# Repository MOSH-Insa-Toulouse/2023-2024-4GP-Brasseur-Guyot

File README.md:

# 2023-2024-4GP-Brasseur-Guyot

Projet capteur low-tech en graphite par Damien Brasseur et Tristan Guyot : le **BG0524-LTG**

### Contexte

Ce capteur a été réalisé, instrumenté et caractérisé dans le cadre d'un projet de 4ème année au département du Génie Physique de l'INSA TOULOUSE, encadré par Jérémie Grisolia, Benjamin Mestre, Arnaud Biganzoli et Cathy Crouzet. Tout le code, schématiques et mesures sont *open source* et réutilisables à volonté.

### Contacts

Damien : brasseu@insa-toulouse.fr <br>
Tristan : tguyot@insa-toulouse.fr

### Table des matières

[Description générale du projet](#coo) <br>
[Caractéristiques techniques](#zozo) <br>
[Mode d'emploi](#pookie) <br>
[Tests du capteur graphite](#booboo)

## 1 - Description générale du projet <a name="coo">

### Principe

Les capteurs sont partout. Dès qu’on cherche à automatiser un système, quel qu’il soit, on a besoin de capteurs. Pourtant, la plupart sont très coûteux en énergie, et leur multiplication fait qu’ils sont de plus en plus impactants sur l’environnement. C’est pour ça que les capteurs low-tech représentent un atout non négligeable. 

Un dépôt de graphite sur du papier forme un système granulaire, composé de grains de plus ou moins grande taille espacés d'une certaine distance, appelée distance inter-grain.
Cette propriété fait que sa conductance dépend de façon exponentielle de la distance inter-grain, qui peut être modulée en repliant le papier.
Ainsi, on peut retrouver la contrainte appliquée au matériau directement en mesurant la résistance aux bornes du capteur.

### Contenu du banc

 <br>

 - Le capteur graphite (interchangeable)
 - Un amplificateur permettant de mesurer avec précision les variations (cette amplification peut être modulée via la modification de la résistance R2 de la boucle de rétroaction de l'amplificateur, pilotée grâce à l'encodeur rotatoire)
 - Un capteur flex-sensor permettant de comparer les mesures du capteur graphite
 - Un écran OLED, sur lequel les mesures sont affichées en temps-réel
 - Une application Android, connectée en Bluetooth, sur laquelle les mesures et leur variation peuvent être visionnée

## 2 - Caractéristiques techniques <a name="zozo">

La *datasheet* est accessible [ici](./Datasheet/datasheet_capteur-graphite_final.pdf)

### Capteur

Le capteur est constitué d'une feuille de papier recouverte de graphite déposé au crayon selon un patterne spécifique :

 <br>

L'épaisseur du papier utilisé est de 200 µm.

### Electronique

L'électronique analogique permettant d'amplifier et de filtrer le signal du capteur graphite est composé d'un amplificateur transimpédance LTC1050 et de trois filtres :
 - Un filtre passif en entrée permettant d'éviter la distortion dans l'étage d'entrée
 - Un filtre actif basé sur l'amplificateur permettant une efficacité maximale
 - Un filtre passif en sortie pour éliminer le bruit introduit lors du traitement.

 <br>

### KiCad

Explications disponibles [ici](https://github.com/MOSH-Insa-Toulouse/2023-2024-4GP-Brasseur-Guyot/tree/main/KiCad)

### Code Arduino

Explications disponibles [ici](https://github.com/MOSH-Insa-Toulouse/2023-2024-4GP-Brasseur-Guyot/tree/main/Code%20Arduino)

### Application Android

Explications disponibles [ici](https://github.com/MOSH-Insa-Toulouse/2023-2024-4GP-Brasseur-Guyot/tree/main/Application%20Android)

## 3 - Mode d'emploi <a name="pookie">

### KiCad

Le dossier KiCad est à télécharger dans son intégralité.
Une fois téléchargé, il faudra recharger les librairies de symboles depuis le dossier Mods.

### Code Arduino

Pour charger le code sur la carte **Arduino UNO**, rien de plus facile ! Il suffit de l'ouvrir dans l'application Arduino IDE avec la carte branchée en USB, puis cliquer sur *Upload*.

### Application Android

L'application est à télécharger sur un téléphone Android. Après l'installation, aller dans les paramètres des applications Android et accorder l'accès au Bluetooth et au micro à l'application.
Pour assurer la connexion entre la carte Arduino et le téléphone, il faut d'abord se connecter au module Bluetooth de la carte avec l'interface générale Bluetooth du téléphone. Ensuite, on pourra sélectionner dans l'application le module et on pourra commencer à s'amuser.

## 4 - Tests du capteur graphite <a name="booboo">

Nous avons réalisé des mesures de compression et de détente avec des capteurs comportant différentes densités de graphite (variant avec le type de crayon : 4H, HB et 4B), ainsi que pour le Flex sensor.

Le banc de test sur lequel nous avons testé les mesures comporte 4 demi-cercles de diamètres 2cm, 3cm, 4cm et 5cm, respectivement. La déformation est calculée selon l'expression suivante : $\varepsilon = \frac{D}{e}$ avec $D$ diamètre du demi-cercle et $e$ épaisseur du papier.

Voici la caractéristique en détente : 

 <br>

On remarque que la variation de résistance la plus marquée (pente la plus élevée) est cele du capteur au crayon 4H. De façon surprenante, le capteur au cayon HB est moins efficace que le capteur 4B.

Voici la caractéristique en compression : 

 <br>

Même comportement, sauf qu'une limite a été atteinte en mesure de compression (demi-cercle de 2cm) avec le capteur 4H. Le flex sensor ne fonctionnant que dans un seul sens, nous n'avons pas pu le tester dans ces conditions.

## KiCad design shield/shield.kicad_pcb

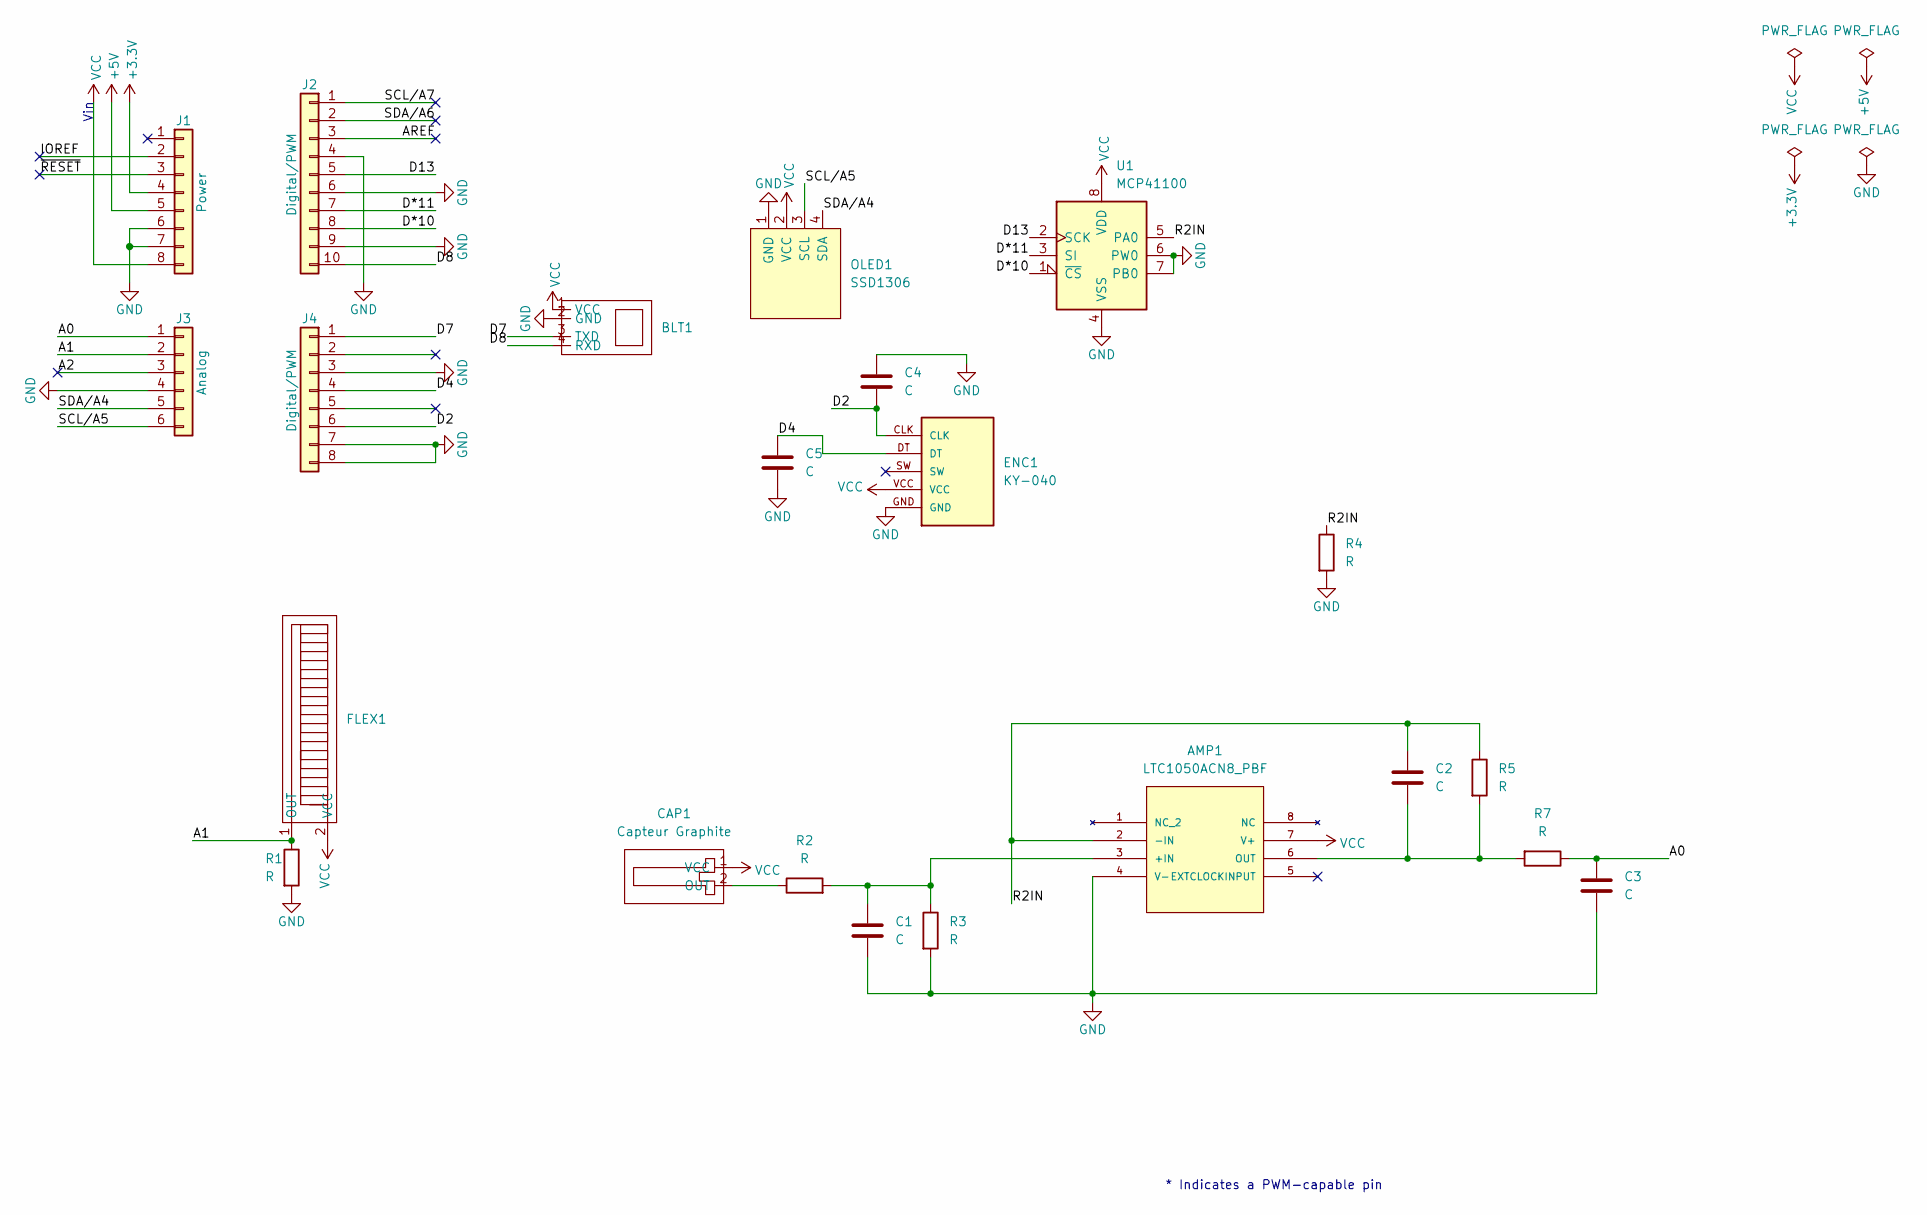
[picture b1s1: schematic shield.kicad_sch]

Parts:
AMP1: LTC1050ACN8_PBF; PDIP-8_N; MANUFACTURER_PART_NUMBER ltc1050acn8
BLT1: PinSocket_1x04_P2.54mm_Vertical
C1, C3, C4, C5: C; C_Disc_D4.7mm_W2.5mm_P5.00mm
C2: C; C_Rect_L4.6mm_W3.8mm_P2.50mm_MKS02_FKP02
CAP1: Capteur Graphite; PinSocket_1x02_P2.54mm_Vertical
ENC1: KY-040; KY-040-PORT
FLEX1: PinSocket_1x02_P2.54mm_Vertical
J1: Power; PinSocket_1x08_P2.54mm_Vertical
J2: Digital/PWM; PinSocket_1x10_P2.54mm_Vertical
J3: Analog; PinSocket_1x06_P2.54mm_Vertical
J4: Digital/PWM; PinSocket_1x08_P2.54mm_Vertical
OLED1: SSD1306; 128x64OLED
R1, R3, R4, R5: R; R_Axial_DIN0207_L6.3mm_D2.5mm_P2.54mm_Vertical
R2, R7: R; R_Axial_DIN0207_L6.3mm_D2.5mm_P5.08mm_Vertical
U1: MCP41100; DIP-8_W7.62mm_LongPads

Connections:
+3V3: J1.4
+5V: J1.5
/A0: C3.1, J3.1, R7.1
/A1: FLEX1.1 (OUT), J3.2, R1.1
/A2: J3.3
/AREF: J2.3
/D2: C4.2, ENC1.CLK, J4.6
/D4: C5.1, ENC1.DT, J4.4
/D7: BLT1.3 (TXD), J4.1
/D8: BLT1.4 (RXD), J2.10
/D13: J2.5, U1.2 (SCK)
/D*10: J2.8, U1.1 (~CS)
/D*11: J2.7, U1.3 (SI)
/IOREF: J1.2
/R2IN: AMP1.2 (-IN), C2.1, R4.1, R5.1, U1.5 (PA0)
/SCL/A5: J3.6, OLED1.3 (SCL)
/SCL/A7: J2.1
/SDA/A4: J3.5, OLED1.4 (SDA)
/SDA/A6: J2.2
/~RESET: J1.3
GND: AMP1.4 (V-), BLT1.2 (GND), C1.2, C3.2, C4.1, C5.2, ENC1.GND, J1.6, J1.7, J2.4, J2.6, J2.9, J3.4, J4.3, J4.7, J4.8, OLED1.1 (GND), R1.2, R3.2, R4.2, U1.4 (VSS), U1.6 (PW0), U1.7 (PB0)
unnamed: AMP1.3 (+IN), C1.1, R2.2, R3.1
unnamed: AMP1.6 (OUT), C2.2, R5.2, R7.2
unnamed: CAP1.2 (OUT), R2.1
VCC: AMP1.7 (V+), BLT1.1 (VCC), CAP1.1 (VCC), ENC1.VCC, FLEX1.2 (VCC), J1.8, OLED1.2 (VCC), U1.8 (VDD)

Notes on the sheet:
* Indicates a PWM-capable pin
Vin

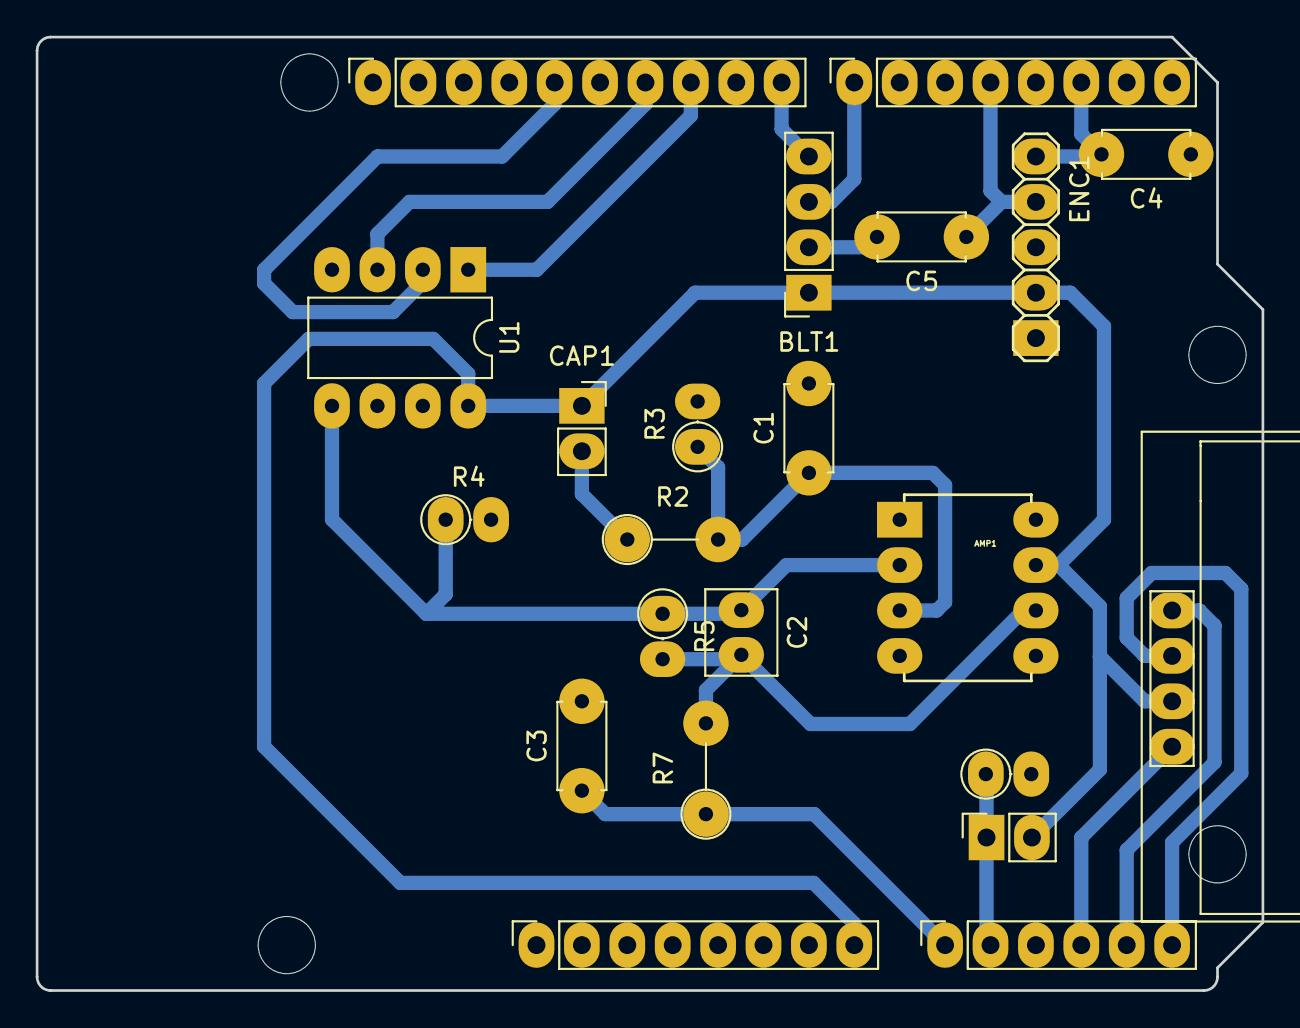
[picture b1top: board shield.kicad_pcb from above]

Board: 2 copper layers, 68.6 x 53.3 mm, 26 parts (0 on the bottom side), 17 nets.

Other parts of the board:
MH1, MH2, MH3, MH4: MountingHole_3.2mm

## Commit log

2024-03-13 Add files via upload
    First commit
2024-03-18 Ajout du kicad du shield
    Penser à recharger les librairies de symboles après téléchargement
2024-03-18 Rename capteur_graphite.ino to code/capteur_graphite.ino
2024-03-18 Changement de nom
2024-03-18 Update README.md
    Une fois télécharger c'est pas français
2024-04-01 Update README.md
    Added main structure to README
2024-04-01 Rename capteur_graphite.ino to capteur_graphite.ino
2024-04-01 Update capteur_graphite.ino
    Changed info to be sent over Bluetooth and other small changes
2024-04-01 Added Android app file
2024-04-01 Added logo image
2024-04-08 Added .aia (project file) and .apk (app package)
2024-05-25 Added test bench
2024-05-25 Added images
2024-05-26 datasheet

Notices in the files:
parts and their libraries:
COPYRIGHT: Copyright C 2016 Accelerated Designs. All rights reserved
